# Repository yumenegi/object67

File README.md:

# object67
Object 67 is an attempt at an AES-67-2013 compliant network D/AC studios and home audio.

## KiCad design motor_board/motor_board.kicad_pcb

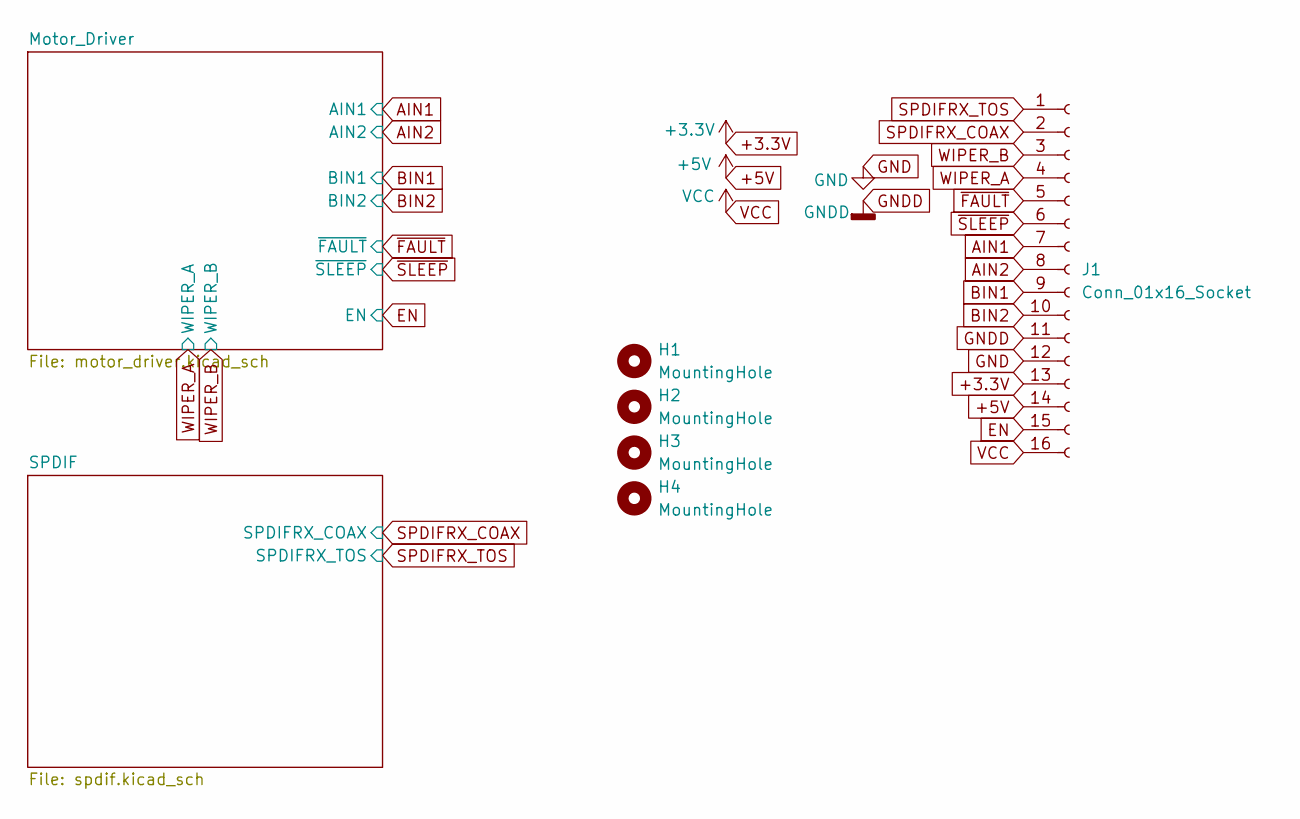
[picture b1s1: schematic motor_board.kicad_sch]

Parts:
H1, H2, H3, H4: MountingHole; MountingHole_3.2mm_M3
J1: Conn_01x16_Socket; JST_PH_S16B-PH-K_1x16_P2.00mm_Horizontal

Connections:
+3.3V: J1.13; also elsewhere on the board
+5V: J1.14; also elsewhere on the board
AIN1: J1.7; also elsewhere on the board
AIN2: J1.8; also elsewhere on the board
BIN1: J1.9; also elsewhere on the board
BIN2: J1.10; also elsewhere on the board
EN: J1.15; also elsewhere on the board
GND: J1.12; also elsewhere on the board
GNDD: J1.11; also elsewhere on the board
SPDIFRX_COAX: J1.2; also elsewhere on the board
SPDIFRX_TOS: J1.1; also elsewhere on the board
VCC: J1.16; also elsewhere on the board
WIPER_A: J1.4; also elsewhere on the board
WIPER_B: J1.3; also elsewhere on the board
~FAULT: J1.5; also elsewhere on the board
~SLEEP: J1.6; also elsewhere on the board

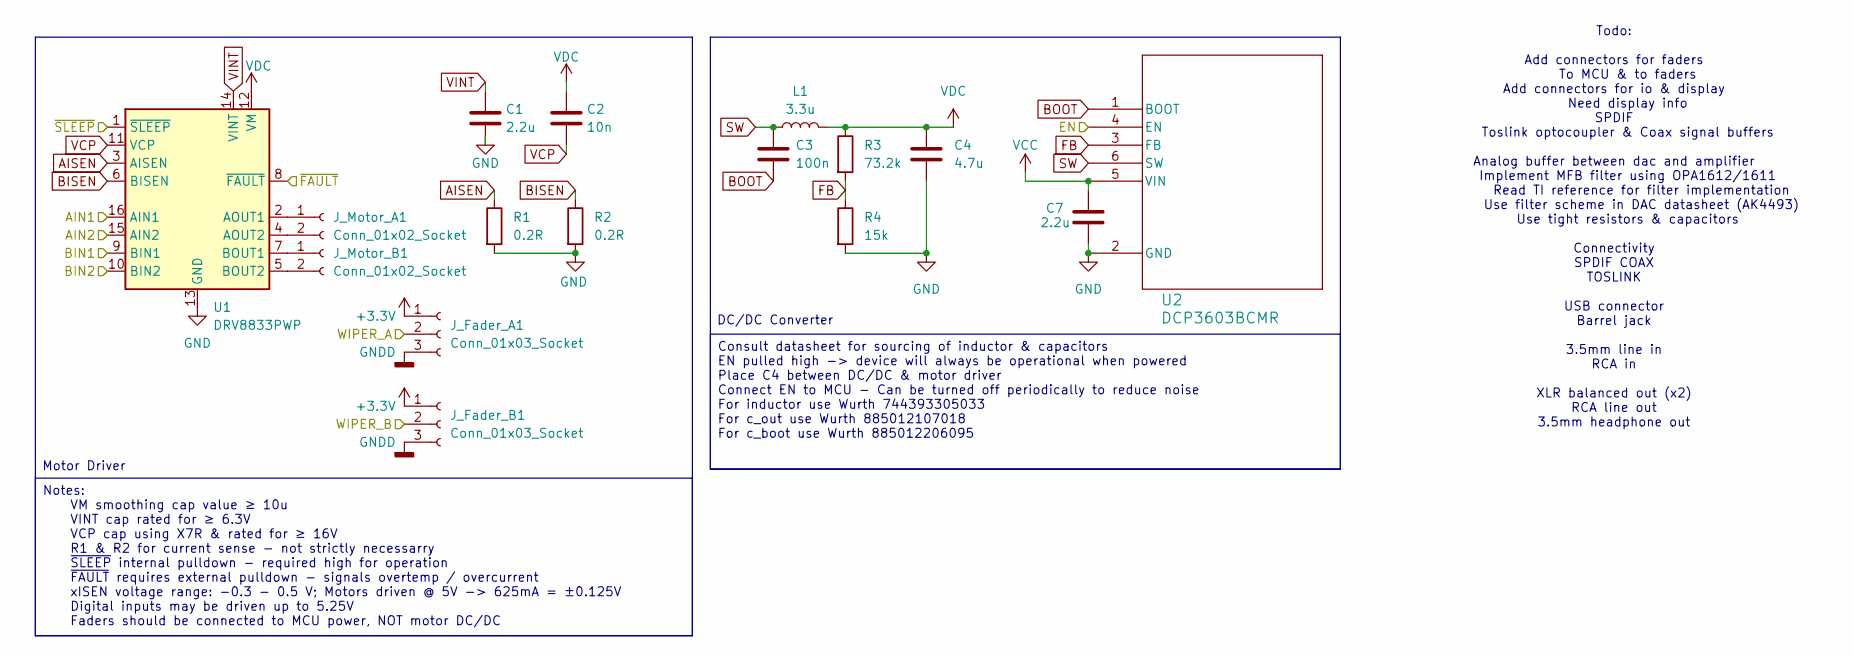
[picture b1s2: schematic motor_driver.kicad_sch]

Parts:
C1, C7: 2.2u; C_0805_2012Metric_Pad1.18x1.45mm_HandSolder
C2: 10n; C_0805_2012Metric_Pad1.18x1.45mm_HandSolder
C3: 100n; C_0603_1608Metric_Pad1.08x0.95mm_HandSolder
C4: 4.7u; C_0805_2012Metric_Pad1.18x1.45mm_HandSolder
J_Fader_A1: Conn_01x03_Socket; JST_PH_B3B-PH-K_1x03_P2.00mm_Vertical
J_Fader_B1: Conn_01x03_Socket; JST_PH_B3B-PH-K_1x03_P2.00mm_Vertical
J_Motor_A1: Conn_01x02_Socket; JST_PH_B2B-PH-K_1x02_P2.00mm_Vertical
J_Motor_B1: Conn_01x02_Socket; JST_PH_B2B-PH-K_1x02_P2.00mm_Vertical
L1: 3.3u; 744393665033
R1, R2: 0.2R; R_2512_6332Metric_Pad1.40x3.35mm_HandSolder
R3: 73.2k; R_0402_1005Metric_Pad0.72x0.64mm_HandSolder
R4: 15k; R_0402_1005Metric_Pad0.72x0.64mm_HandSolder
U1: DRV8833PWP; HTSSOP-16-1EP_4.4x5mm_P0.65mm_EP3.4x5mm_Mask2.46x2.31mm_The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
U2: DCP3603BCMR; SOT23-6L_1p7x3p01_STM

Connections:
+3.3V: J_Fader_A1.1, J_Fader_B1.1; also elsewhere on the board
AIN1: U1.16 (AIN1); also elsewhere on the board
AIN2: U1.15 (AIN2); also elsewhere on the board
AISEN: R1.1, U1.3 (AISEN)
BIN1: U1.9 (BIN1); also elsewhere on the board
BIN2: U1.10 (BIN2); also elsewhere on the board
BISEN: R2.1, U1.6 (BISEN)
BOOT: C3.2, U2.1 (BOOT)
EN: U2.4 (EN); also elsewhere on the board
FB: R3.2, R4.1, U2.3 (FB)
GND: C1.2, C4.2, C7.2, R1.2, R2.2, R4.2, U1.13 (GND), U1.17 (GND), U2.2 (GND); also elsewhere on the board
GNDD: J_Fader_A1.3, J_Fader_B1.3; also elsewhere on the board
unnamed: J_Motor_A1.1, U1.2 (AOUT1)
unnamed: J_Motor_A1.2, U1.4 (AOUT2)
unnamed: J_Motor_B1.1, U1.7 (BOUT1)
unnamed: J_Motor_B1.2, U1.5 (BOUT2)
SW: C3.1, L1.1, U2.6 (SW)
VCC: C7.1, U2.5 (VIN); also elsewhere on the board
VCP: C2.2, U1.11 (VCP)
VDC: C2.1, C4.1, L1.2, R3.1, U1.12 (VM)
VINT: C1.1, U1.14 (VINT)
WIPER_A: J_Fader_A1.2; also elsewhere on the board
WIPER_B: J_Fader_B1.2; also elsewhere on the board
~FAULT: U1.8 (~FAULT); also elsewhere on the board
~SLEEP: U1.1 (~SLEEP); also elsewhere on the board

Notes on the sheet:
DC/DC Converter
Motor Driver
Todo: Add connectors for faders To MCU & to faders Add connectors for io & display Need display info SPDIF Toslink optocoupler & Coax signal buffers Analog buffer between dac and amplifier Implement MFB filter using OPA1612/1611 Read TI reference for filter implementation Use filter scheme in DAC d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
Notes: VM smoothing cap value ≥ 10u VINT cap rated for ≥ 6.3V VCP cap using X7R & rated for ≥ 16V R1 & R2 for current sense - not strictly necessarry ~{SLEEP} internal pulldown - required high for operation ~{FAULT} requires external pulldown - signals overtemp / overcurrent xISEN voltage range: -0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
Consult datasheet for sourcing of inductor & capacitors EN pulled high -> device will always be operational when powered Place C4 between DC/DC & motor driver Connect EN to MCU - Can be turned off periodically to reduce noise For inductor use Wurth 744393305033 For c_out use Wurth 885012107018 For 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

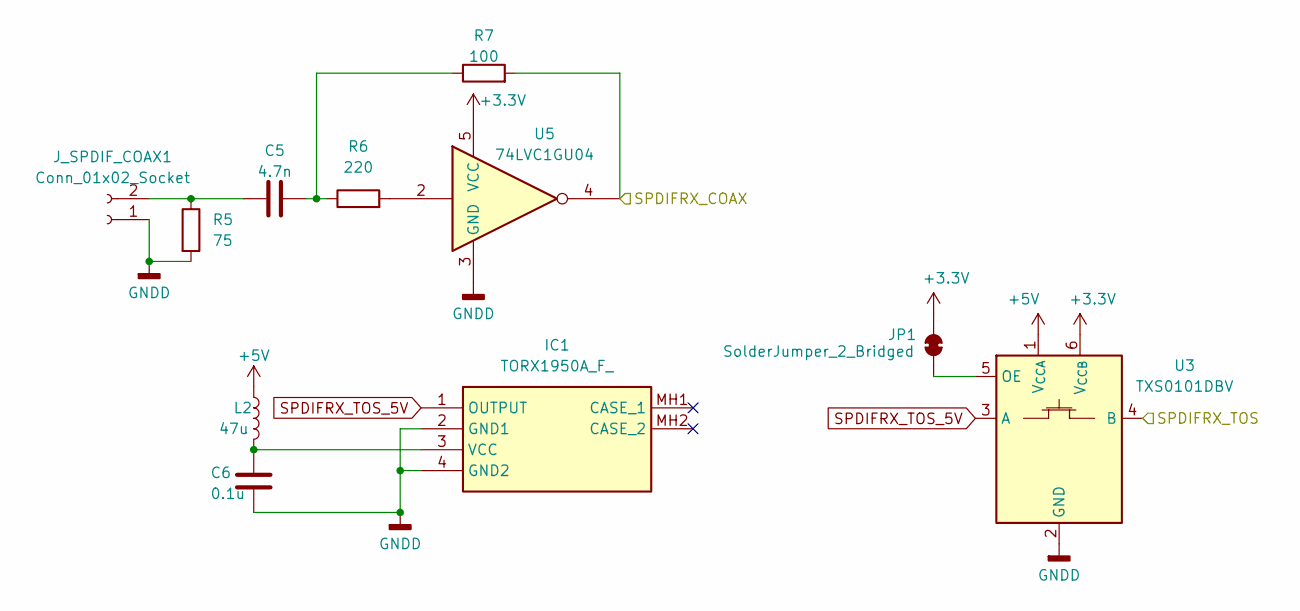
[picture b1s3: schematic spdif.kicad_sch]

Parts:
C5: 4.7n; C_0805_2012Metric_Pad1.18x1.45mm_HandSolder
C6: 0.1u; C_0603_1608Metric_Pad1.08x0.95mm_HandSolder
IC1: TORX1950A_F_; TORX1950AF; Manufacturer_Part_Number TORX1950A(F); Mouser Part Number 71-TORX1950A(F)
JP1: SolderJumper_2_Bridged; SolderJumper-2_P1.3mm_Bridged_RoundedPad1.0x1.5mm
J_SPDIF_COAX1: Conn_01x02_Socket; JST_PH_B2B-PH-K_1x02_P2.00mm_Vertical
L2: 47u; L_Vishay_IHLP-4040
R5: 75; R_0805_2012Metric_Pad1.20x1.40mm_HandSolder
R6: 220; R_0805_2012Metric_Pad1.20x1.40mm_HandSolder
R7: 100; R_0805_2012Metric_Pad1.20x1.40mm_HandSolder
U3: TXS0101DBV; SOT-23-6
U5: 74LVC1GU04; SOT-23-5

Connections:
+3.3V: JP1.2 (B), U3.6 (V_{CCB}), U5.5 (VCC); also elsewhere on the board
+5V: L2.1, U3.1 (V_{CCA}); also elsewhere on the board
GNDD: C6.2, IC1.2 (GND1), IC1.4 (GND2), J_SPDIF_COAX1.1, R5.2, U3.2 (GND), U5.3 (GND); also elsewhere on the board
unnamed: C5.2, R6.1, R7.1
unnamed: C6.1, IC1.3 (VCC), L2.2
unnamed: JP1.1 (A), U3.5 (OE)
unnamed: C5.1, J_SPDIF_COAX1.2, R5.1
unnamed: R6.2, U5.2
SPDIFRX_COAX: R7.2, U5.4; also elsewhere on the board
SPDIFRX_TOS: U3.4 (B); also elsewhere on the board
SPDIFRX_TOS_5V: IC1.1 (OUTPUT), U3.3 (A)

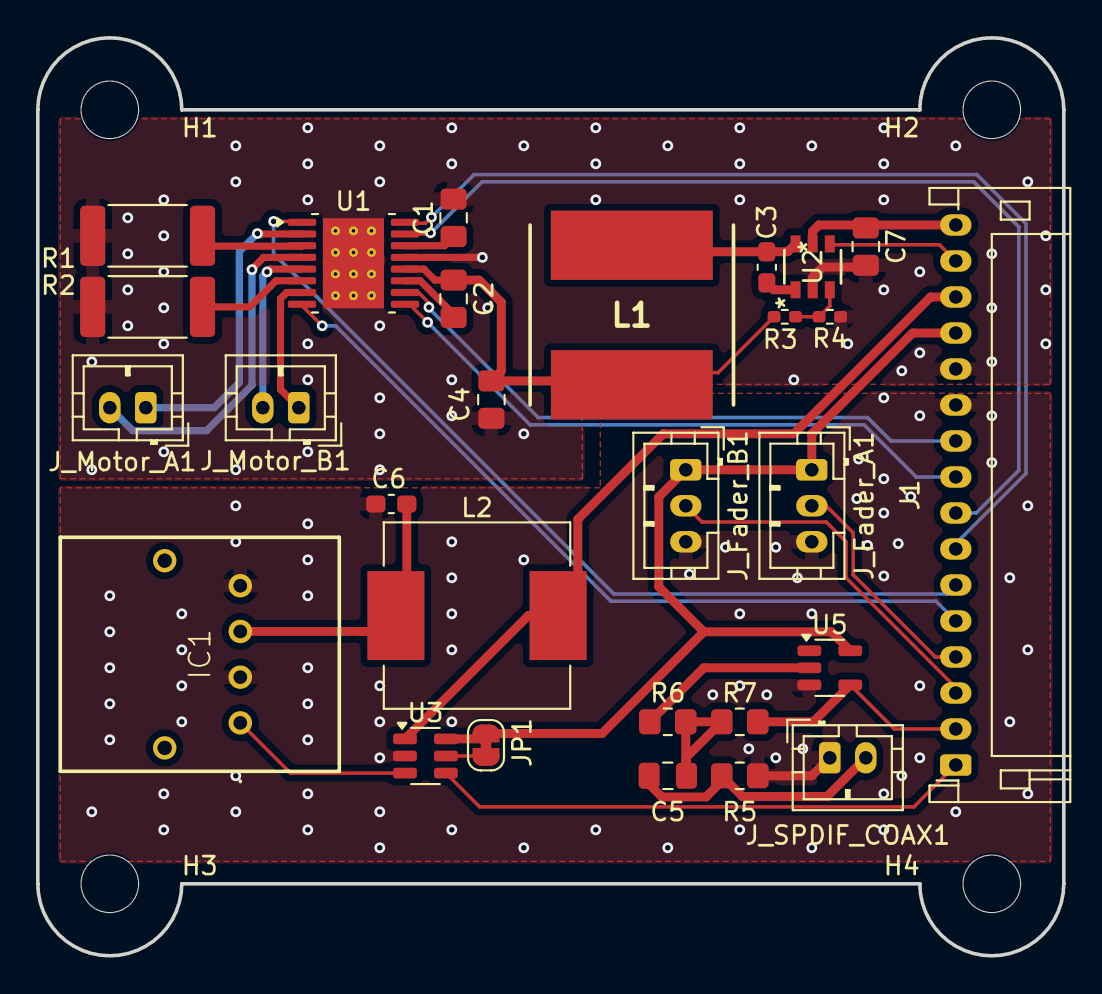
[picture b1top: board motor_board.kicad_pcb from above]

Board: 2 copper layers, 57.0 x 51.0 mm, 32 parts (0 on the bottom side), 34 nets.

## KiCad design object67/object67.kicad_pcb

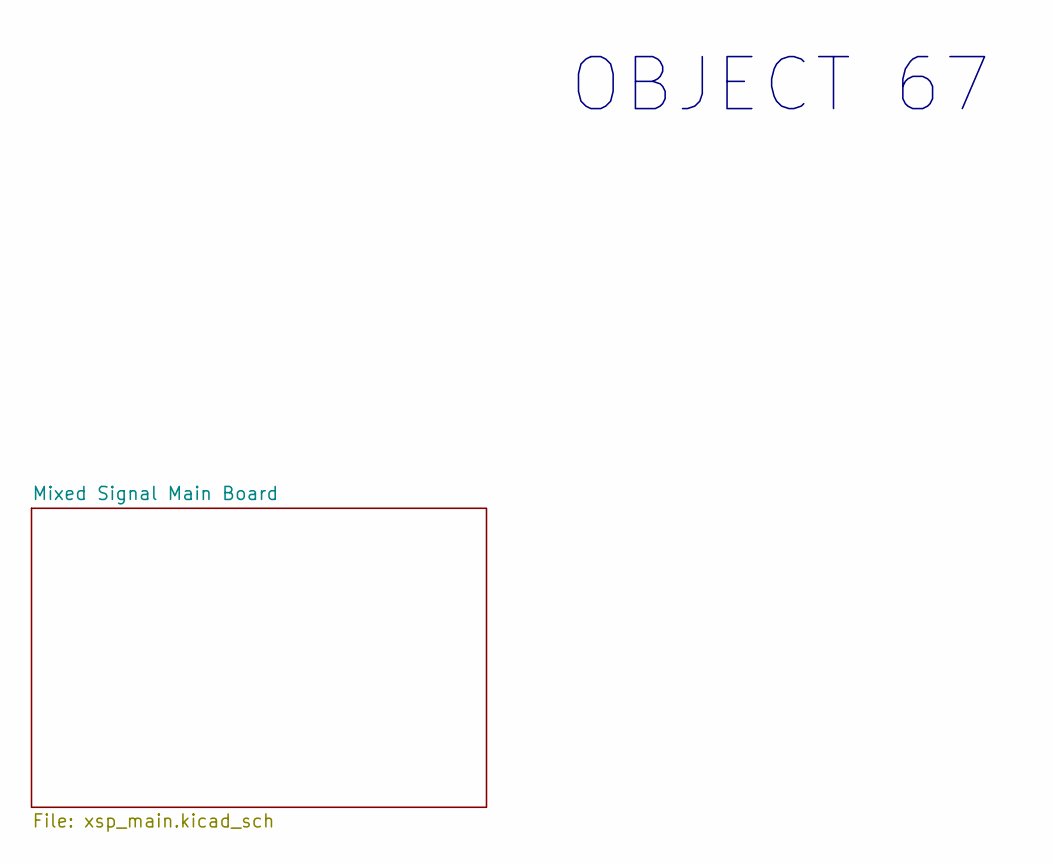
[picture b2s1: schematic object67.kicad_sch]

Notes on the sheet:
OBJECT 67

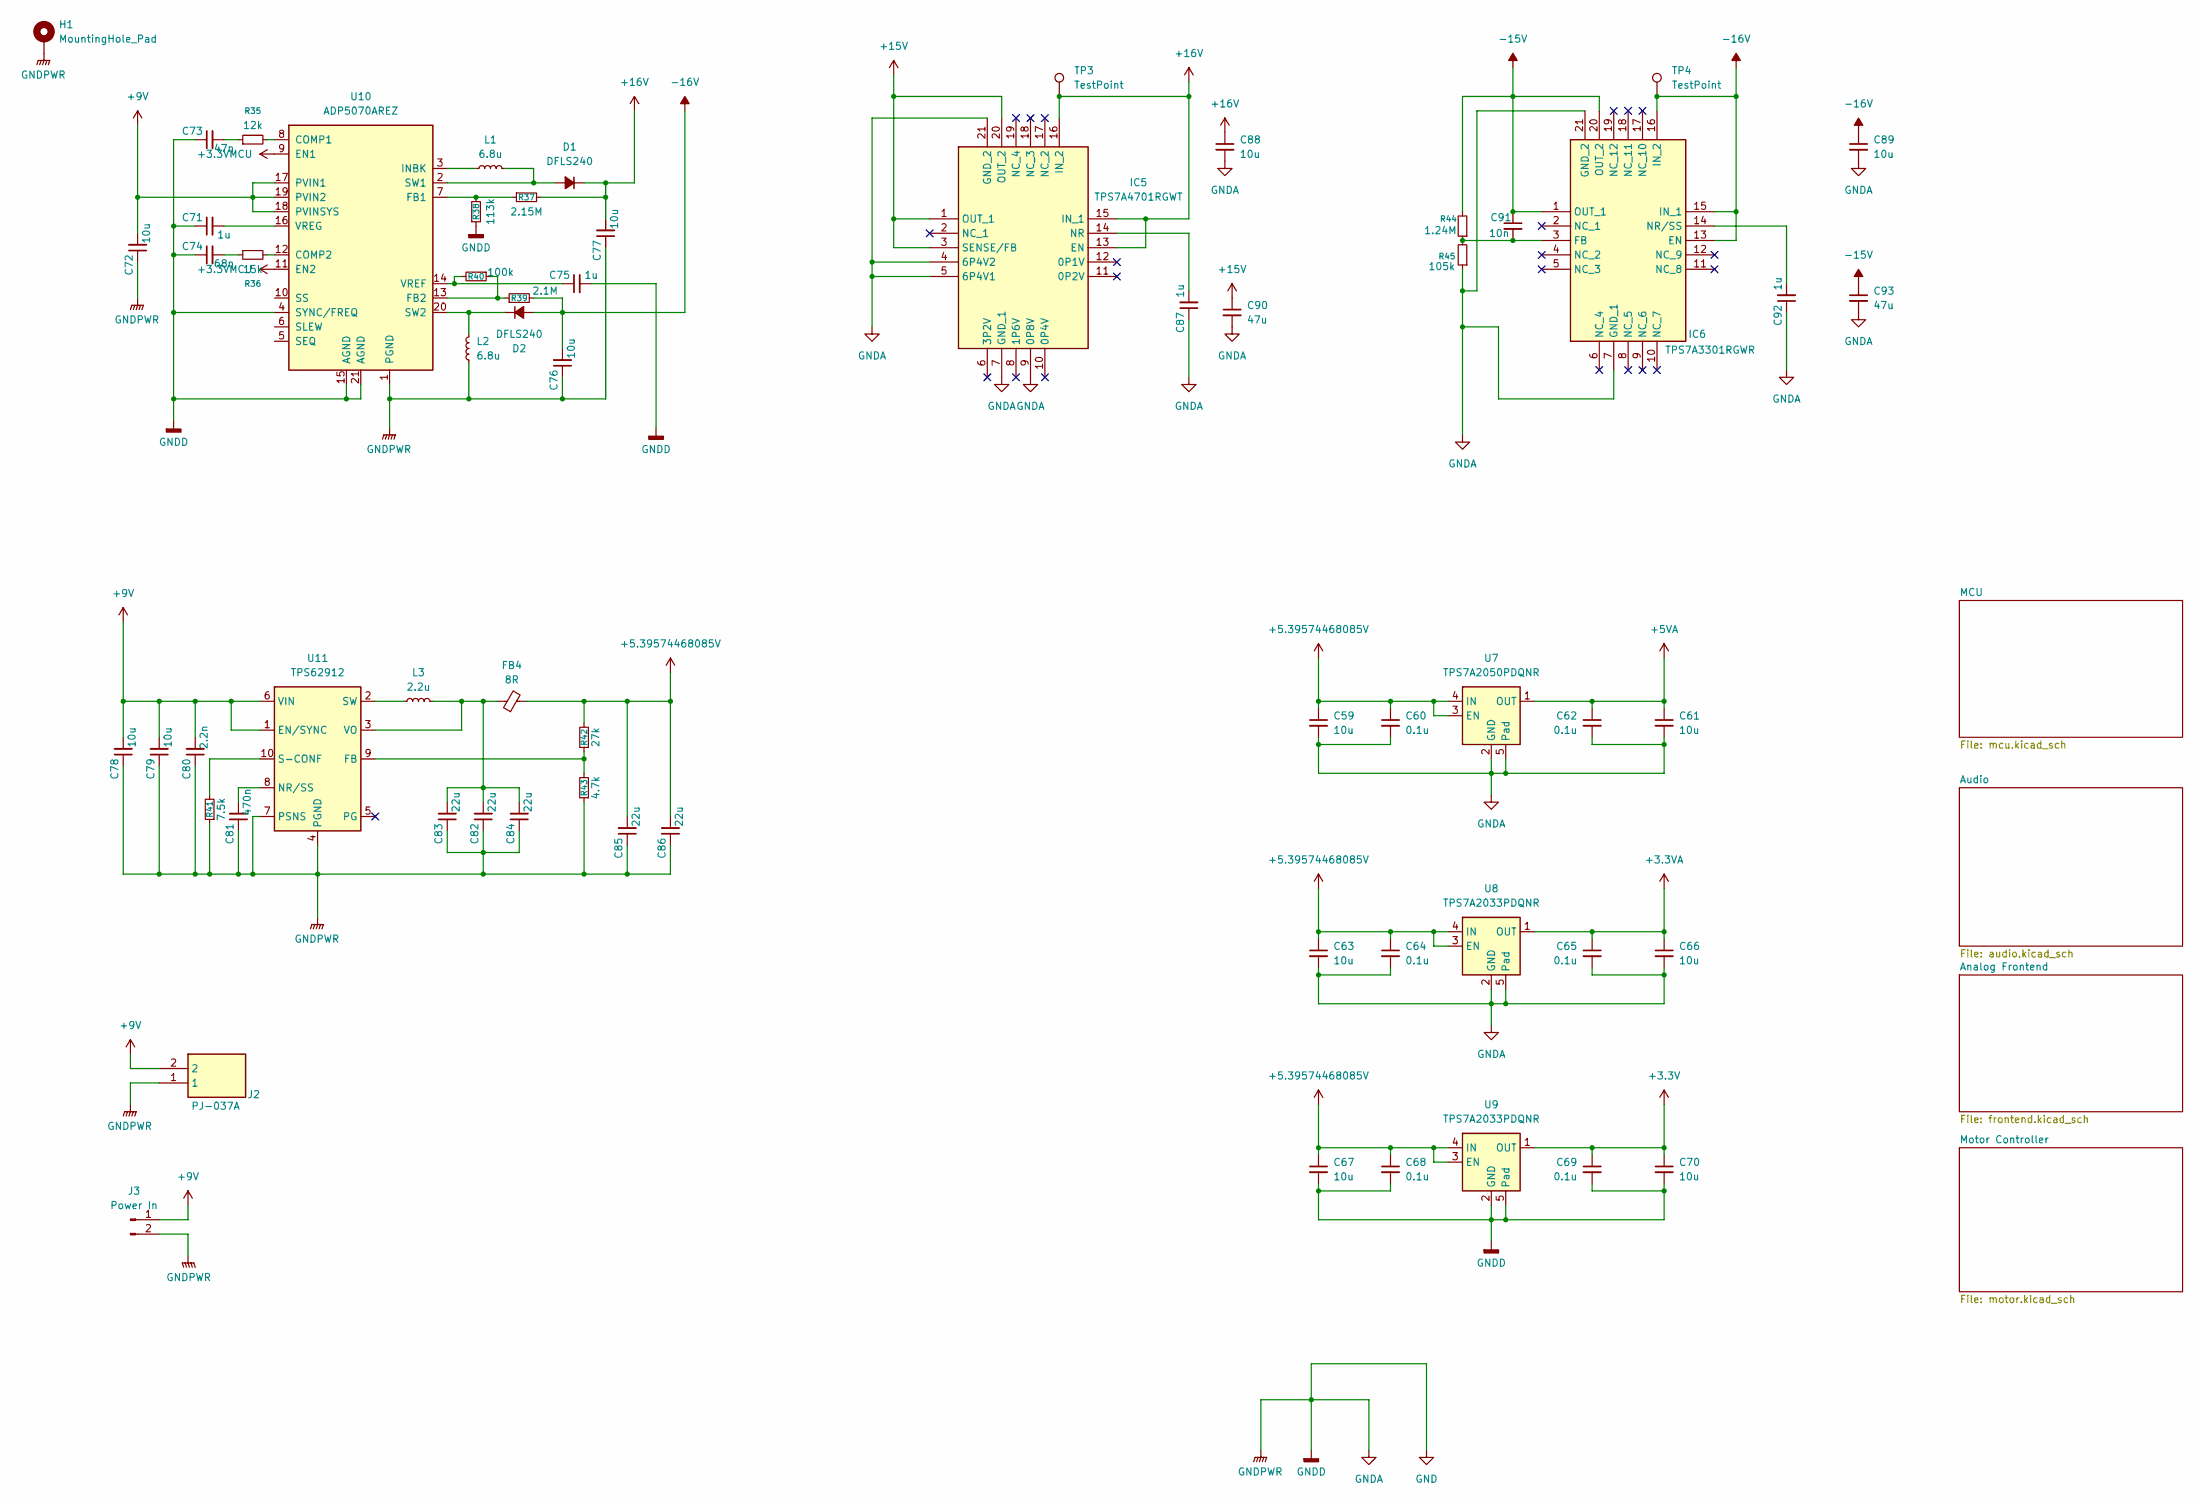
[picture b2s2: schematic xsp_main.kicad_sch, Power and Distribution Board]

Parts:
C59, C61, C63, C66, C67, C70: 10u; C_0603_1608Metric
C60, C62, C64, C65, C68, C69: 0.1u; C_0603_1608Metric
C71, C75: 1u; C_0603_1608Metric
C72, C78, C79: 10u; C_0805_2012Metric
C73: 47n; C_0603_1608Metric
C74: 68n; C_0603_1608Metric
C76, C77, C88, C89: 10u; C_1206_3216Metric
C80: 2.2n; C_0402_1005Metric
C81: 470n; C_0805_2012Metric
C82, C83, C84, C85, C86: 22u; C_0805_2012Metric
C87: 1u; C_0805_2012Metric
C90, C93: 47u; C_1206_3216Metric
C91: 10n; C_0402_1005Metric
C92: 1u; C_1206_3216Metric
D1, D2: DFLS240; D_PowerDI-123
FB4: 8R; L_0603_1608Metric
H1: MountingHole_Pad; MountingHole_4.3mm_M4_ISO7380_Pad_TopOnly
IC5: TPS7A4701RGWT; QFN65P500X500X100-21N-D; Manufacturer_Part_Number TPS7A4701RGWT; Mouser Part Number 595-TPS7A4701RGWT
IC6: TPS7A3301RGWR; QFN65P500X500X100-21N-D; Manufacturer_Part_Number TPS7A3301RGWR; Mouser Part Number 595-TPS7A3301RGWR
J2: PJ-037A; PJ037A; Manufacturer_Part_Number PJ-037A; Mouser Part Number 490-PJ-037A
J3: Power In; TestPoint_2Pads_Pitch5.08mm_Drill1.3mm
L1, L2: 6.8u; L_Wuerth_MAPI-4030
L3: 2.2u; L_Wuerth_MAPI-4030
R35: 12k; R_0603_1608Metric
R36: 15k; R_0603_1608Metric
R37: 2.15M; R_0603_1608Metric
R38: 113k; R_0603_1608Metric
R39: 2.1M; R_0603_1608Metric
R40: 100k; R_0603_1608Metric
R41: 7.5k; R_0603_1608Metric
R42: 27k; R_0603_1608Metric
R43: 4.7k; R_0603_1608Metric
R44: 1.24M; R_0805_2012Metric
R45: 105k; R_0805_2012Metric
TP3, TP4: TestPoint; TestPoint_Pad_D1.0mm
U7: TPS7A2050PDQNR; Texas_X2SON-4_1x1mm_P0.65mm
U8, U9: TPS7A2033PDQNR; Texas_X2SON-4_1x1mm_P0.65mm
U10: ADP5070AREZ; SOP65P640X120-21N
U11: TPS62912; Texas_RPU0010A_VQFN-HR-10_2x2mm_P0.5mm

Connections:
+3.3V: C69.1, C70.1, U9.1 (OUT); also elsewhere on the board
+3.3VA: C65.1, C66.1, U8.1 (OUT); also elsewhere on the board
+3.3VMCU: U10.9 (EN1), U10.11 (EN2); also elsewhere on the board
+5.39574468085V: C59.1, C60.1, C63.1, C64.1, C67.1, C68.1, C85.2, C86.2, FB4.2, R42.2, U7.3 (EN), U7.4 (IN), U8.3 (EN), U8.4 (IN), U9.3 (EN), U9.4 (IN); also elsewhere on the board
+5VA: C61.1, C62.1, U7.1 (OUT); also elsewhere on the board
+15V: C90.1, IC5.1 (OUT_1), IC5.3 (SENSE/FB), IC5.20 (OUT_2); also elsewhere on the board
+16V: C77.2, C88.1, D1.1 (K), IC5.13 (EN), IC5.15 (IN_1), IC5.16 (IN_2), R37.2, TP3.1
-15V: C91.1, C93.1, IC6.1 (OUT_1), IC6.20 (OUT_2), R44.2; also elsewhere on the board
-16V: C76.2, C89.1, D2.2 (A), IC6.13 (EN), IC6.15 (IN_1), IC6.16 (IN_2), R39.2, TP4.1
GND: C59.2, C60.2, C61.2, C62.2, C63.2, C64.2, C65.2, C66.2, C67.2, C68.2, C69.2, C70.2, C71.1, C72.1, C73.1, C74.1, C75.2, C76.1, C77.1, C78.1, C79.1, C80.1, C81.1, C82.1, C83.1, C84.1, C85.1, C86.1, C87.1, C88.2, C89.2, C90.2, C92.1, C93.2, H1.1, IC5.4 (6P4V2), IC5.5 (6P4V1), IC5.7 (GND_1), IC5.9 (0P8V), IC5.21 (GND_2), IC6.7 (GND_1), IC6.21 (GND_2), J2.1, J3.2, L2.1, R38.1, R41.1, R43.1, R45.1, U7.2 (GND), U7.5 (Pad), U8.2 (GND), U8.5 (Pad), U9.2 (GND), U9.5 (Pad), U10.1 (PGND), U10.4 (SYNC/FREQ), U10.15 (AGND), U10.21 (AGND), U11.4 (PGND), U11.7 (PSNS); also elsewhere on the board
unnamed: C73.2, R35.1
unnamed: C74.2, R36.1
unnamed: D1.2 (A), L1.2, U10.2 (SW1)
unnamed: D2.1 (K), L2.2, U10.20 (SW2)
unnamed: C87.2, IC5.14 (NR)
unnamed: C91.2, IC6.3 (FB), R44.1, R45.2
unnamed: C92.2, IC6.14 (NR/SS)
unnamed: R35.2, U10.8 (COMP1)
unnamed: R36.2, U10.12 (COMP2)
unnamed: R37.1, R38.2, U10.7 (FB1)
unnamed: R39.1, R40.1, U10.13 (FB2)
unnamed: L1.1, U10.3 (INBK)
unnamed: C75.1, R40.2, U10.14 (VREF)
unnamed: C71.2, U10.16 (VREG)
unnamed: R42.1, R43.2, U11.9 (FB)
unnamed: C81.2, U11.8 (NR/SS)
unnamed: R41.2, U11.10 (S-CONF)
unnamed: L3.1, U11.2 (SW)
unnamed: C82.2, C83.2, C84.2, FB4.1, L3.2, U11.3 (VO)
VIN: C72.2, C78.2, C79.2, C80.2, J2.2, J3.1, U10.17 (PVIN1), U10.18 (PVINSYS), U10.19 (PVIN2), U11.1 (EN/SYNC), U11.6 (VIN); also elsewhere on the board

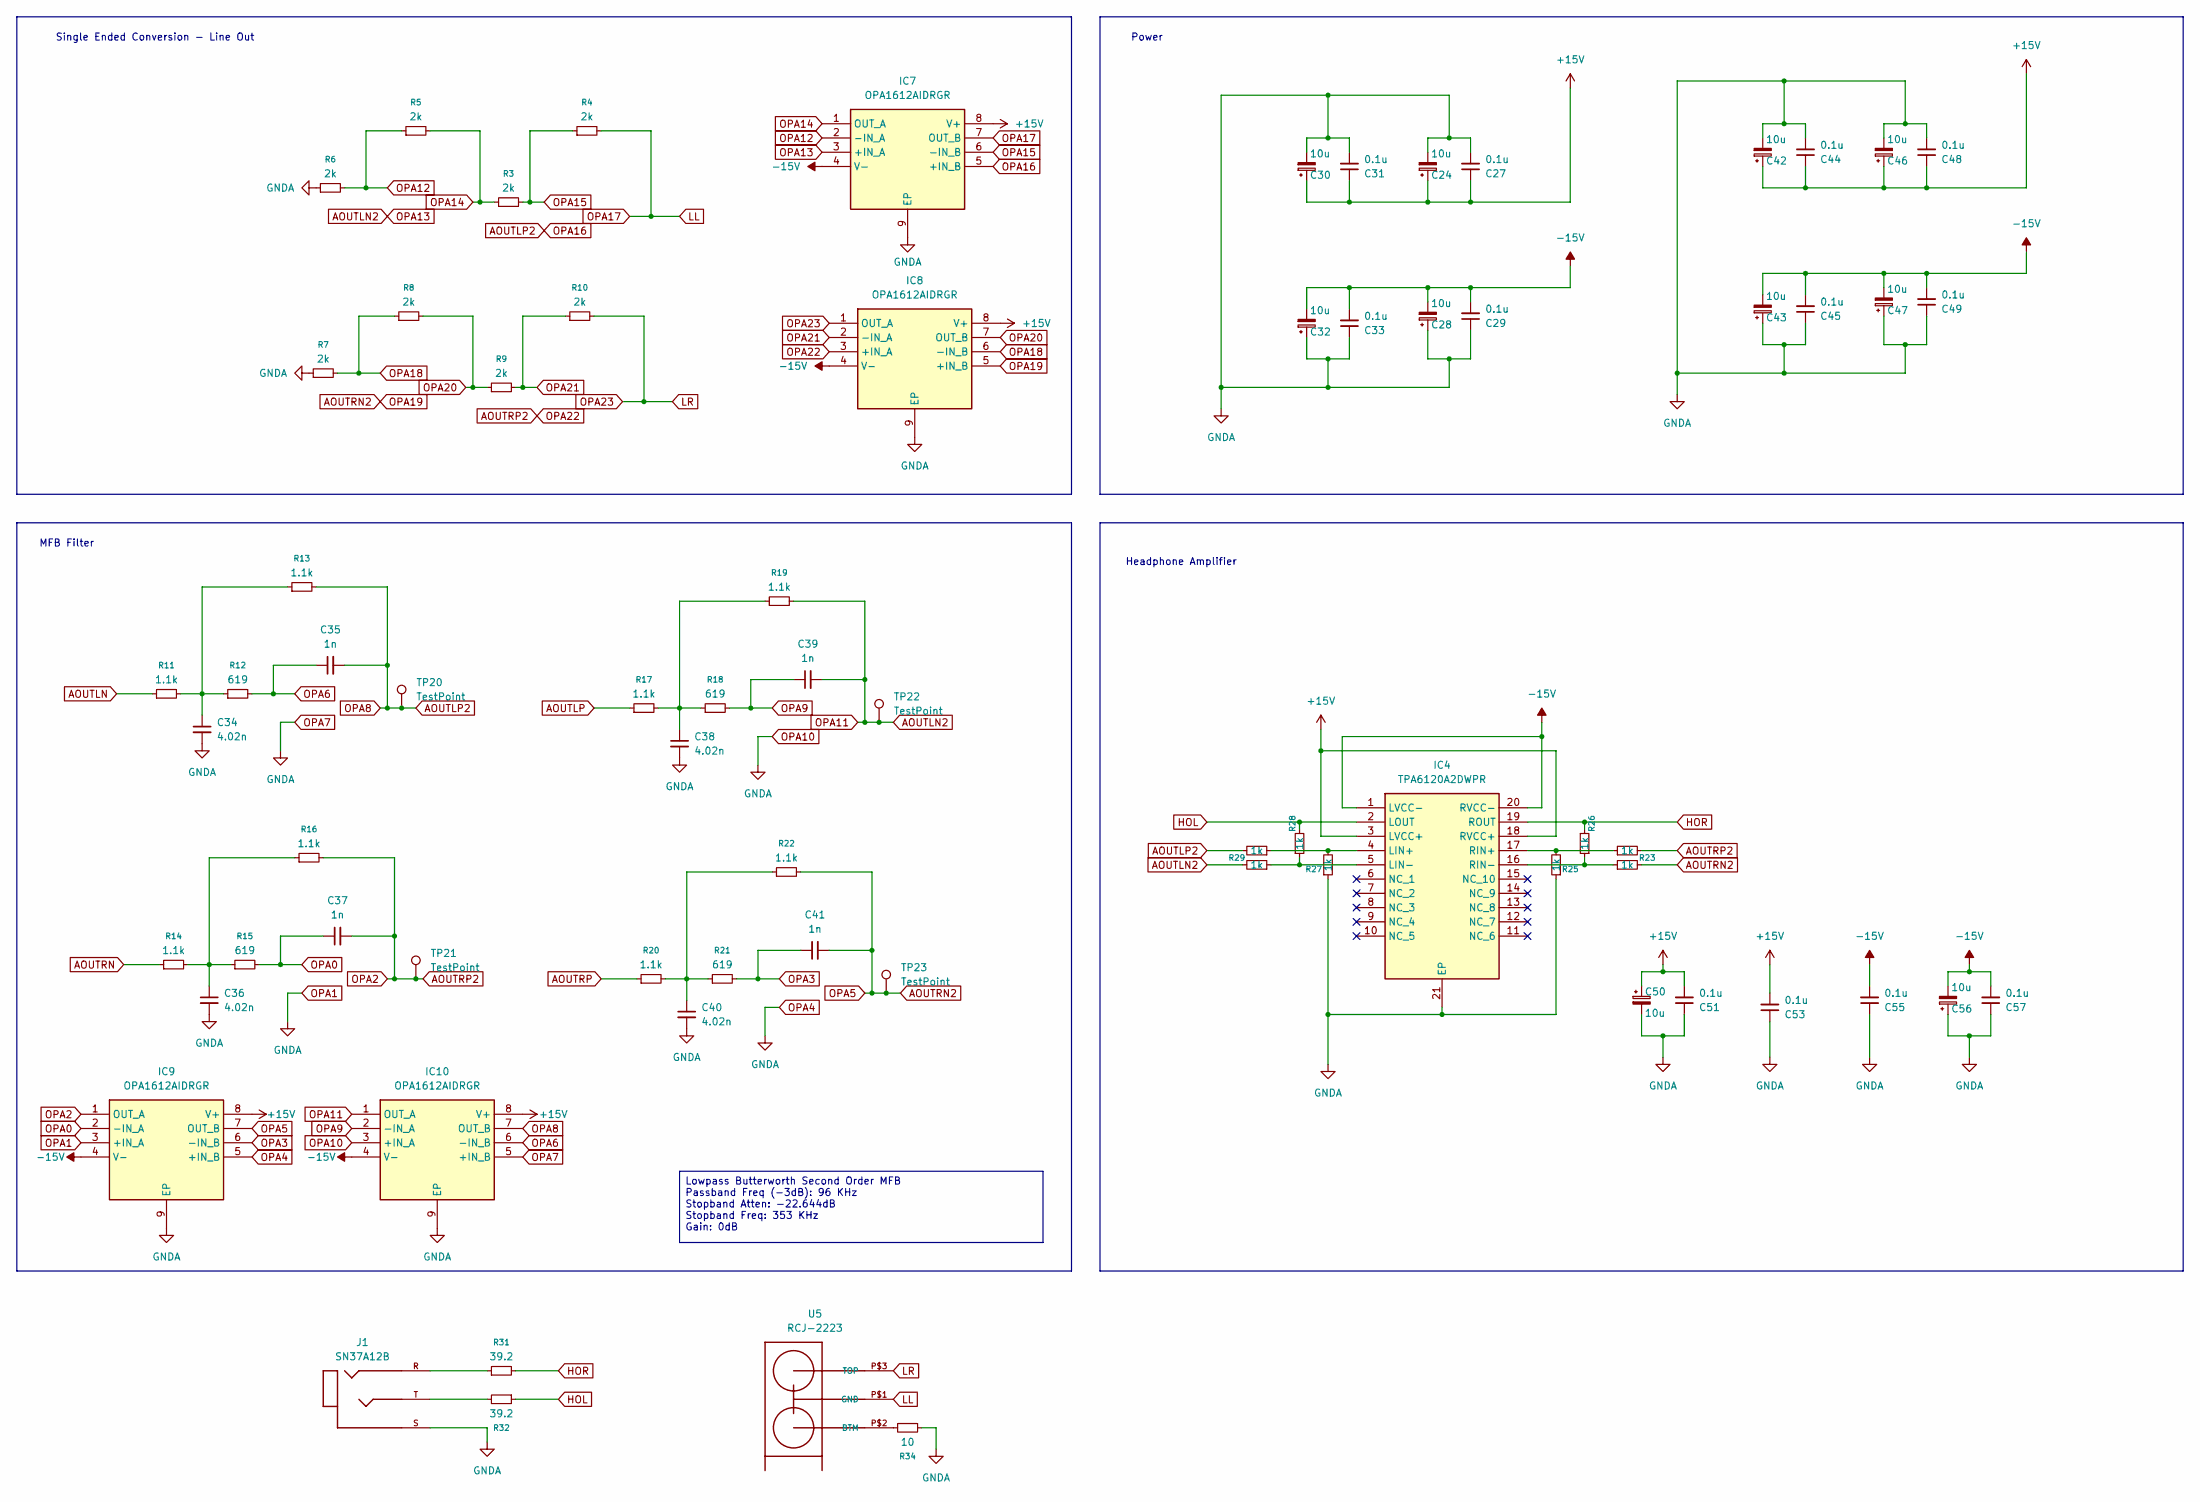
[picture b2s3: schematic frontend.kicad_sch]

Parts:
C24, C28, C30, C32, C42, C43, C46, C47, C50, C56: 10u; CP_Elec_4x5.3
C27, C29, C31, C33, C44, C45, C48, C49, C51, C53, C55, C57: 0.1u; C_0603_1608Metric
C34, C36, C38, C40: 4.02n; C_0805_2012Metric
C35, C37, C39, C41: 1n; C_0805_2012Metric
IC4: TPA6120A2DWPR; SOIC127P1040X275-21N; Manufacturer_Part_Number TPA6120A2DWPR; Mouser Part Number 595-TPA6120A2DWPR
IC7, IC8, IC9, IC10: OPA1612AIDRGR; WSON-8-1EP_3x3mm_P0.5mm_EP1.2x2mm_ThermalVias; Manufacturer_Part_Number OPA1612AIDRGR; Mouser Part Number 595-OPA1612AIDRGR
J1: SN37A12B; SWITCHCRAFT_SN37A12B; PARTREV F
R3, R4, R5, R6, R7, R8, R9, R10: 2k; R_0603_1608Metric
R11, R13, R14, R16, R17, R19, R20, R22: 1.1k; R_1206_3216Metric
R12, R15, R18, R21: 619; R_1206_3216Metric
R23, R24, R25, R26, R27, R28, R29, R30: 1k; R_0805_2012Metric
R31, R32: 39.2; R_1206_3216Metric
R34: 10; R_1206_3216Metric
TP20, TP21, TP22, TP23: TestPoint; TestPoint_Pad_D1.0mm
U5: RCJ-2223; DUALRCA

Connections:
+15V: C24.1, C27.1, C30.1, C31.1, C42.1, C44.1, C46.1, C48.1, C50.1, C51.2, C53.2, IC4.3 (LVCC+), IC4.18 (RVCC+), IC7.8 (V+), IC8.8 (V+), IC9.8 (V+), IC10.8 (V+); also elsewhere on the board
-15V: C28.2, C29.2, C32.2, C33.2, C43.2, C45.2, C47.2, C49.2, C55.2, C56.2, C57.2, IC4.1 (LVCC-), IC4.20 (RVCC-), IC7.4 (V-), IC8.4 (V-), IC9.4 (V-), IC10.4 (V-); also elsewhere on the board
AOUTLN: R11.1; also elsewhere on the board
AOUTLN2: C39.2, IC7.3 (+IN_A), IC10.1 (OUT_A), R19.2, R30.2, TP22.1
AOUTLP: R17.1; also elsewhere on the board
AOUTLP2: C35.2, IC7.5 (+IN_B), IC10.7 (OUT_B), R13.2, R29.2, TP20.1
AOUTRN: R14.1; also elsewhere on the board
AOUTRN2: C41.2, IC8.5 (+IN_B), IC9.7 (OUT_B), R22.2, R24.2, TP23.1
AOUTRP: R20.1; also elsewhere on the board
AOUTRP2: C37.2, IC8.3 (+IN_A), IC9.1 (OUT_A), R16.2, R23.2, TP21.1
GND: C24.2, C27.2, C28.1, C29.1, C30.2, C31.2, C32.1, C33.1, C34.2, C36.2, C38.2, C40.2, C42.2, C43.1, C44.2, C45.1, C46.2, C47.1, C48.2, C49.1, C50.2, C51.1, C53.1, C55.1, C56.1, C57.1, IC4.21 (EP), IC7.9 (EP), IC8.9 (EP), IC9.3 (+IN_A), IC9.5 (+IN_B), IC9.9 (EP), IC10.3 (+IN_A), IC10.5 (+IN_B), IC10.9 (EP), J1.S, R6.1, R7.1, R25.1, R27.1, R34.1; also elsewhere on the board
HOL: IC4.2 (LOUT), R28.2, R32.1
HOR: IC4.19 (ROUT), R26.2, R31.2
LL: IC7.7 (OUT_B), R4.2, U5.P$1 (GND)
LR: IC8.1 (OUT_A), R10.2, U5.P$3 (TOP)
unnamed: C34.1, R11.2, R12.1, R13.1
unnamed: C36.1, R14.2, R15.1, R16.1
unnamed: C38.1, R17.2, R18.1, R19.1
unnamed: C40.1, R20.2, R21.1, R22.1
unnamed: IC4.4 (LIN+), R27.2, R29.1
unnamed: IC4.5 (LIN-), R28.1, R30.1
unnamed: IC4.17 (RIN+), R23.1, R25.2
unnamed: IC4.16 (RIN-), R24.1, R26.1
unnamed: J1.R, R31.1
unnamed: J1.T, R32.2
unnamed: R34.2, U5.P$2 (BTM)
OPA0: C37.1, IC9.2 (-IN_A), R15.2
OPA3: C41.1, IC9.6 (-IN_B), R21.2
OPA6: C35.1, IC10.6 (-IN_B), R12.2
OPA9: C39.1, IC10.2 (-IN_A), R18.2
OPA12: IC7.2 (-IN_A), R5.1, R6.2
OPA14: IC7.1 (OUT_A), R3.1, R5.2
OPA15: IC7.6 (-IN_B), R3.2, R4.1
OPA18: IC8.6 (-IN_B), R7.2, R8.1
OPA20: IC8.7 (OUT_B), R8.2, R9.1
OPA21: IC8.2 (-IN_A), R9.2, R10.1

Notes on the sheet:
Single Ended Conversion - Line Out
Headphone Amplifier
Power
MFB Filter
Lowpass Butterworth Second Order MFB Passband Freq (-3dB): 96 KHz Stopband Atten: -22.644dB Stopband Freq: 353 KHz Gain: 0dB
